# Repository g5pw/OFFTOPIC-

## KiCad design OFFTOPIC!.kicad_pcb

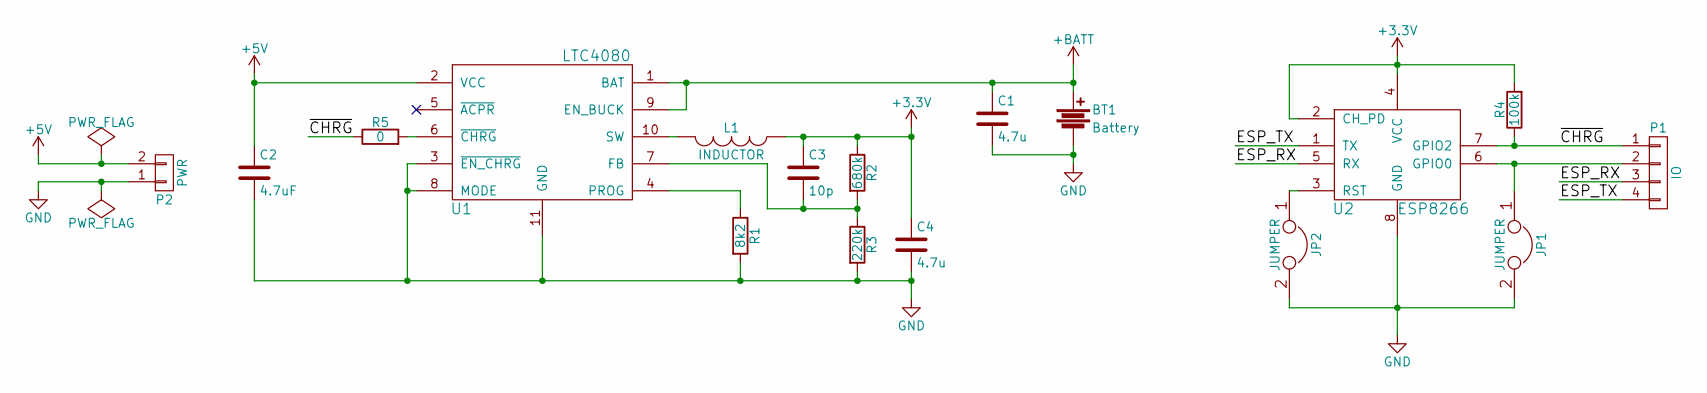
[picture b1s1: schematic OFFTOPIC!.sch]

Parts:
BT1: Battery; Pin_Header_Straight_1x02
C1, C4: 4.7u; C_0402
C2: 4.7uF; C_0402
C3: 10p; C_0402
JP1, JP2: JUMPER; R_0402
L1: INDUCTOR; Neosid_Inductor_SM-NE30_SMD1210
P1: IO; Pin_Header_Straight_1x04
P2: PWR; Pin_Header_Straight_1x02
R1: 8k2; R_0402
R2: 680k; R_0402
R3: 220k; R_0402
R4: 100k; R_0402
R5: 0; R_0402
U1: LTC4080; DFN-10-1EP_3x3mm_Pitch0.5mm
U2: ESP8266; Socket_Strip_Straight_2x04

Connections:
+3V3: C3.1, C4.1, L1.1, R2.1, R4.2, U2.2 (CH_PD), U2.4 (VCC)
+5V: C2.1, P2.2, U1.2 (VCC)
+BATT: BT1.1, C1.1, U1.1 (BAT), U1.9 (EN_BUCK)
/ESP_RX: P1.3, U2.5 (RX)
/ESP_TX: P1.4, U2.1 (TX)
/~CHRG: P1.1, R4.1, R5.1, U2.7 (GPIO2)
GND: BT1.2, C1.2, C2.2, C4.2, JP1.2, JP2.2, P2.1, R1.2, R3.2, U1.3 (~EN_CHRG), U1.8 (MODE), U1.11 (GND), U2.8 (GND)
unnamed: C3.2, R2.2, R3.1, U1.7 (FB)
unnamed: JP1.1, P1.2, U2.6 (GPIO0)
unnamed: JP2.1, U2.3 (RST)
unnamed: L1.2, U1.10 (SW)
unnamed: R1.1, U1.4 (PROG)
unnamed: R5.2, U1.6 (~CHRG)

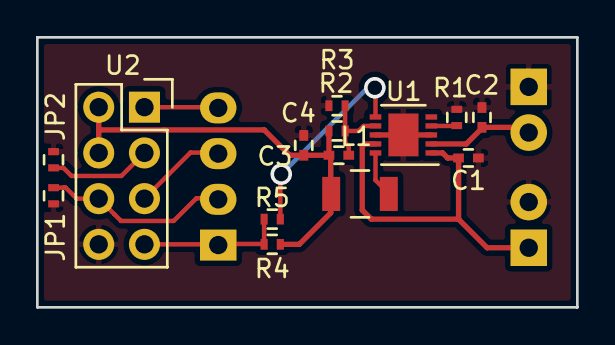
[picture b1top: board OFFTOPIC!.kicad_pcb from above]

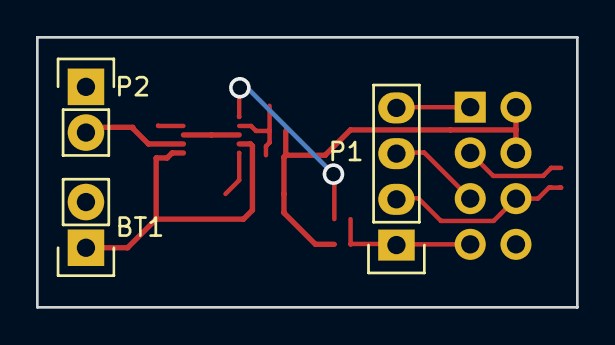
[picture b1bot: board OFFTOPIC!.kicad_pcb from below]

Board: 2 copper layers, 30.0 x 15.0 mm, 17 parts (3 on the bottom side), 13 nets.
